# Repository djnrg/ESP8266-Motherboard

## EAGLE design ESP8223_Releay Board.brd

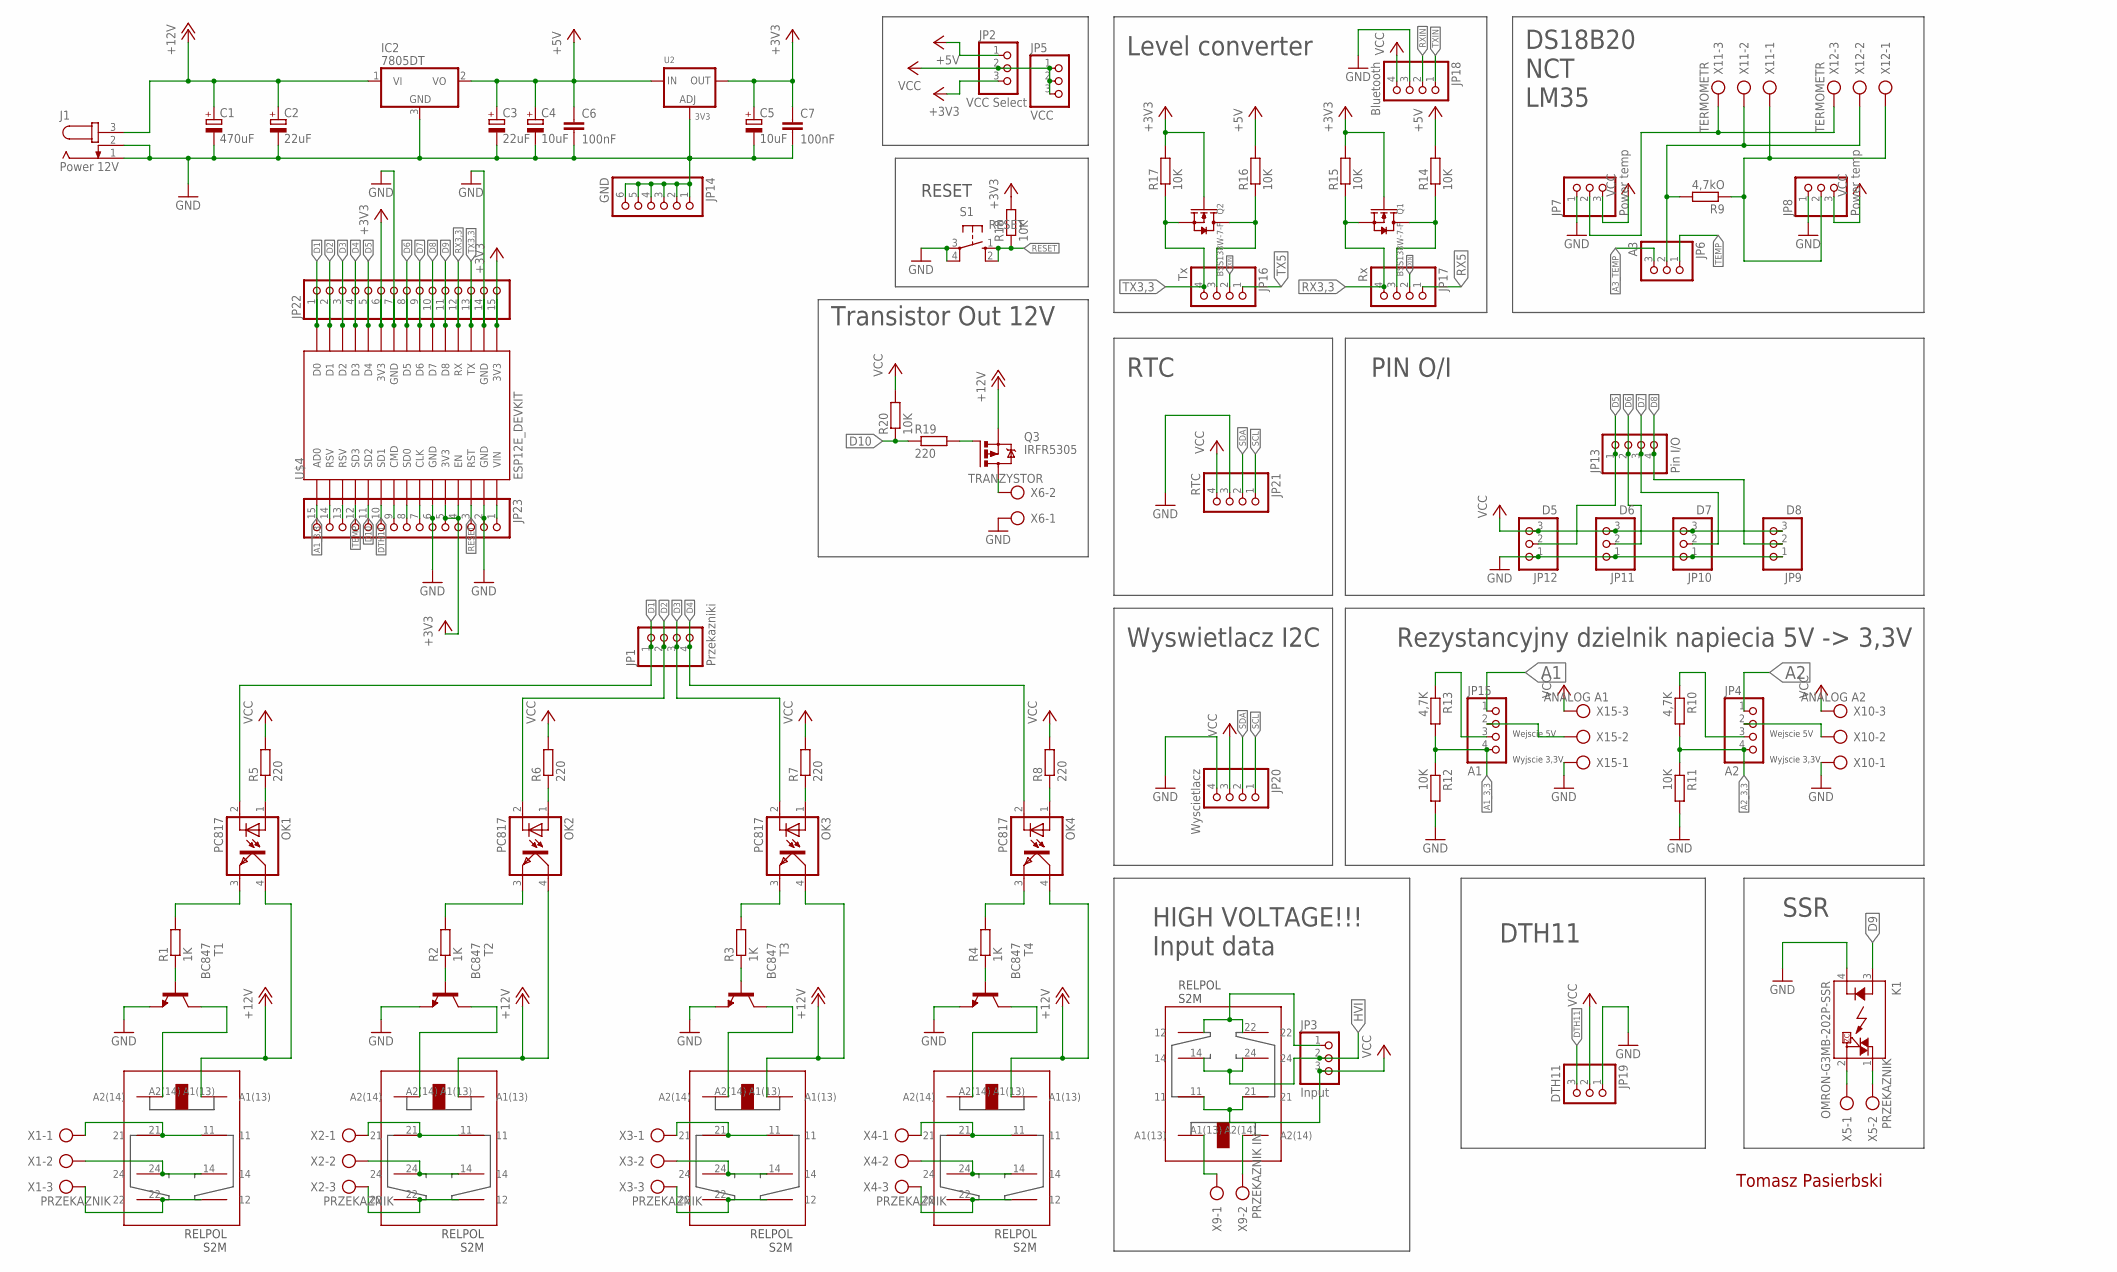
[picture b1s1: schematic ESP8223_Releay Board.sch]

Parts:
C1: 470uF; E5-8,5
C2, C3: 22uF; E2,5-6
C4, C5: 10uF; 153CLV-0810
C6, C7: 100nF; C1206K
IC2: 7805DT; TO252
J1: Power 12V; SPC4077
JP1: Przekazniki; 1X04
JP2: VCC Select; 1X03
JP3: Input; 1X03
JP4: A2; 1X04
JP5: VCC; 1X03
JP6: A3; 1X03
JP7, JP8: Power temp; 1X03
JP9: D8; 1X03
JP10: D7; 1X03
JP11: D6; 1X03
JP12: D5; 1X03
JP13: Pin I/O; 1X04
JP14: GND; 1X06
JP15: A1; 1X04
JP16: Tx; 1X04
JP17: Rx; 1X04
JP18: Bluetooth; 1X04
JP19: DTH11; 1X03
JP20: Wyscietlacz; 1X04
JP21: RTC; 1X04
JP22, JP23: PINHD-1X15; 1X15
K1: OMRON-G3MB-202P-SSR
OK1, OK2, OK3, OK4: PC817; DIL04
Q1, Q2: BSS138W-7-F; SOT-23
Q3: IRFR5305; D-PAK_TO252AA
R1, R2, R3, R4: 1K; R1206W
R5, R6, R7, R8, R19: 220; R1206W
R9: 4,7kO; R1206W
R10, R13: 4,7K; R1206W
R11, R12, R14, R15, R16, R17, R18, R20: 10K; R1206W
S1: RESET; B3F-40XX
T1, T2, T3, T4: BC847; SOT23
U2: 3V3; SOT223-W
U4: RELPOL_S2M; S2M
U$1, U$2, U$3, U$5: RELPOL_S2M; S2M
U$4: ESP12E_DEVKIT
X1, X2, X3, X4: PRZEKAZNIK; AK300/3
X5: PRZEKAZNIK; AK300/2
X6: TRANZYSTOR; AK300/2
X9: PRZEKAZNIK IN; AK300/2
X10: ANALOG A2; AK300/3
X11, X12: TERMOMETR; AK300/3
X15: ANALOG A1; AK300/3

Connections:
+3V3: C5.+, C7.1, JP2.3, JP22.6, JP22.15, JP23.4, JP23.5, Q1.1 (G), Q2.1 (G), R15.2, R17.2, R18.2, U2.2 (OUT), U$4.3V3@0 (3V3), U$4.3V3@1 (3V3), U$4.3V3@2 (3V3), U$4.EN
+5V: C3.+, C4.+, C6.1, IC2.2 (VO), JP2.1, R14.2, R16.2, U2.3 (IN)
+12V: C1.+, C2.+, IC2.1 (VI), J1.3, OK1.4 (COL), OK2.4 (COL), OK3.4 (COL), OK4.4 (COL), Q3.3 (S), U4.A1(13), U$1.A1(13), U$2.A1(13), U$3.A1(13)
A1: JP15.1
A1_3,3: JP15.4, JP23.15, R12.1, R13.2, U$4.AD0
A2: JP4.1
A2_3,3: JP4.4, R10.2, R11.1
A3_TEMP: JP6.3
D1: JP1.1, JP22.1, OK1.2 (C), U$4.D0
D2: JP1.2, JP22.2, OK2.2 (C), U$4.D1
D3: JP1.3, JP22.3, OK3.2 (C), U$4.D2
D4: JP1.4, JP22.4, OK4.2 (C), U$4.D3
D5: JP12.2, JP13.1, JP22.5, U$4.D4
D6: JP11.2, JP13.2, JP22.8, U$4.D5
D7: JP10.2, JP13.3, JP22.9, U$4.D6
D8: JP9.2, JP13.4, JP22.10, U$4.D7
D9: JP22.11, K1.3 (A), U$4.D8
D10: JP23.11, R19.1, R20.1, U$4.SD2
DTH11: JP19.3, JP23.10, U$4.SD1
GND: C1.-, C2.-, C3.-, C4.-, C5.-, C6.2, C7.2, IC2.3 (GND), J1.1, J1.2, JP7.1, JP8.1, JP9.1, JP10.1, JP11.1, JP12.1, JP14.1, JP14.2, JP14.3, JP14.4, JP14.5, JP14.6, JP18.3, JP19.1, JP20.4, JP21.3, JP22.7, JP22.14, JP23.2, JP23.6, K1.4 (K), R11.2, R12.2, S1.3, S1.4 (P1), T1.2 (E), T2.2 (E), T3.2 (E), T4.2 (E), U2.1 (ADJ), U$4.GND@0 (GND), U$4.GND@1 (GND), U$4.GND@2 (GND), U$4.GND@3 (GND), X6.1, X10.1, X15.1
HVI: JP3.2, U$5.14, U$5.24
unnamed: JP23.1, U$4.VIN
unnamed: Q3.1 (G), R19.2
unnamed: JP23.7, U$4.CLK
unnamed: JP23.8, U$4.SD0
unnamed: OK1.1 (A), R5.1
unnamed: OK2.1 (A), R6.1
unnamed: OK3.1 (A), R7.1
unnamed: OK4.1 (A), R8.1
unnamed: JP3.1, U$5.12, U$5.22
unnamed: T2.3 (C), U$1.A2(14)
unnamed: T3.3 (C), U$2.A2(14)
unnamed: T4.3 (C), U$3.A2(14)
unnamed: JP23.9, U$4.CMD
unnamed: T1.3 (C), U4.A2(14)
unnamed: JP4.2, X10.2
unnamed: JP23.13, U$4.RSV@1 (RSV)
unnamed: U$5.A1(13), X9.1
unnamed: R1.1, T1.1 (B)
unnamed: R2.1, T2.1 (B)
unnamed: R3.1, T3.1 (B)
unnamed: R4.1, T4.1 (B)
unnamed: OK1.3 (EMIT), R1.2
unnamed: OK2.3 (EMIT), R2.2
unnamed: OK3.3 (EMIT), R3.2
unnamed: OK4.3 (EMIT), R4.2
unnamed: U$5.A2(14), X9.2
unnamed: JP15.2, X15.2
unnamed: JP23.14, U$4.RSV@0 (RSV)
unnamed: U$3.11, U$3.21, X4.1
unnamed: JP17.3, Q1.3 (D), R14.1
unnamed: U$3.14, U$3.24, X4.2
unnamed: U$3.12, U$3.22, X4.3
unnamed: Q3.4 (D), X6.2
unnamed: JP16.3, Q2.3 (D), R16.1
unnamed: JP7.2, X11.3, X12.3
unnamed: U4.11, U4.21, X1.1
unnamed: U4.14, U4.24, X1.2
unnamed: U4.12, U4.22, X1.3
unnamed: K1.2 (DS2), X5.1
unnamed: K1.1 (DS1), X5.2
unnamed: U$1.11, U$1.21, X2.1
unnamed: U$1.14, U$1.24, X2.2
unnamed: U$1.12, U$1.22, X2.3
unnamed: U$2.11, U$2.21, X3.1
unnamed: U$2.14, U$2.24, X3.2
unnamed: U$2.12, U$2.22, X3.3
unnamed: JP6.2, R9.2, X11.2, X12.2
unnamed: JP8.2, R9.1, X11.1, X12.1
unnamed: JP4.3, R10.1
unnamed: JP15.3, R13.1
RESET: JP23.3, R18.1, S1.1 (S), S1.2 (S1), U$4.RST
RX3,3: JP17.4, JP22.12, Q1.2 (S), R15.1, U$4.RX
RX5: JP17.1
RXIN: JP17.2, JP18.2
SCL: JP20.1, JP21.1
SDA: JP20.2, JP21.2
TEMP: JP6.1, JP23.12, U$4.SD3
TX3,3: JP16.4, JP22.13, Q2.2 (S), R17.1, U$4.TX
TX5: JP16.1
TXIN: JP16.2, JP18.1
VCC: JP2.2, JP3.3, JP5.1, JP5.2, JP5.3, JP7.3, JP8.3, JP9.3, JP10.3, JP11.3, JP12.3, JP18.4, JP19.2, JP20.3, JP21.4, R5.2, R6.2, R7.2, R8.2, R20.2, U$5.11, U$5.21, X10.3, X15.3

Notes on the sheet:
HIGH VOLTAGE!!! Input data
DS18B20 NCT LM35
PIN O/I
Rezystancyjny dzielnik napiecia 5V -> 3,3V
Wejscie 5V
Wyjscie 3,3V
Level converter
SSR
DTH11
RTC
Wyswietlacz I2C
RESET
Transistor Out 12V
Tomasz Pasierbski

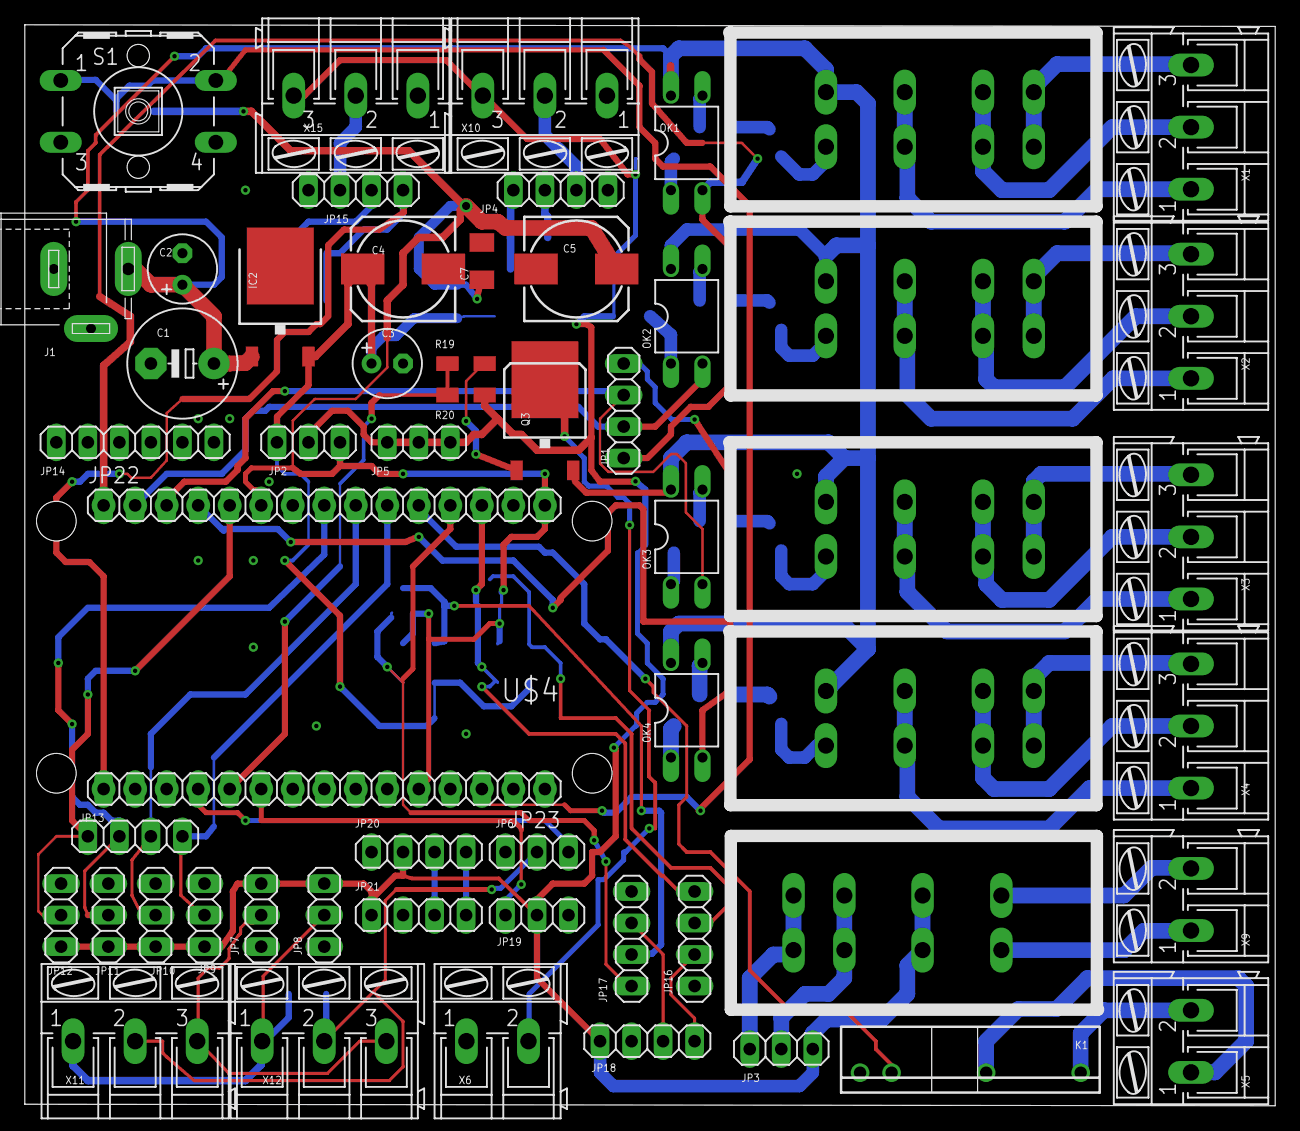
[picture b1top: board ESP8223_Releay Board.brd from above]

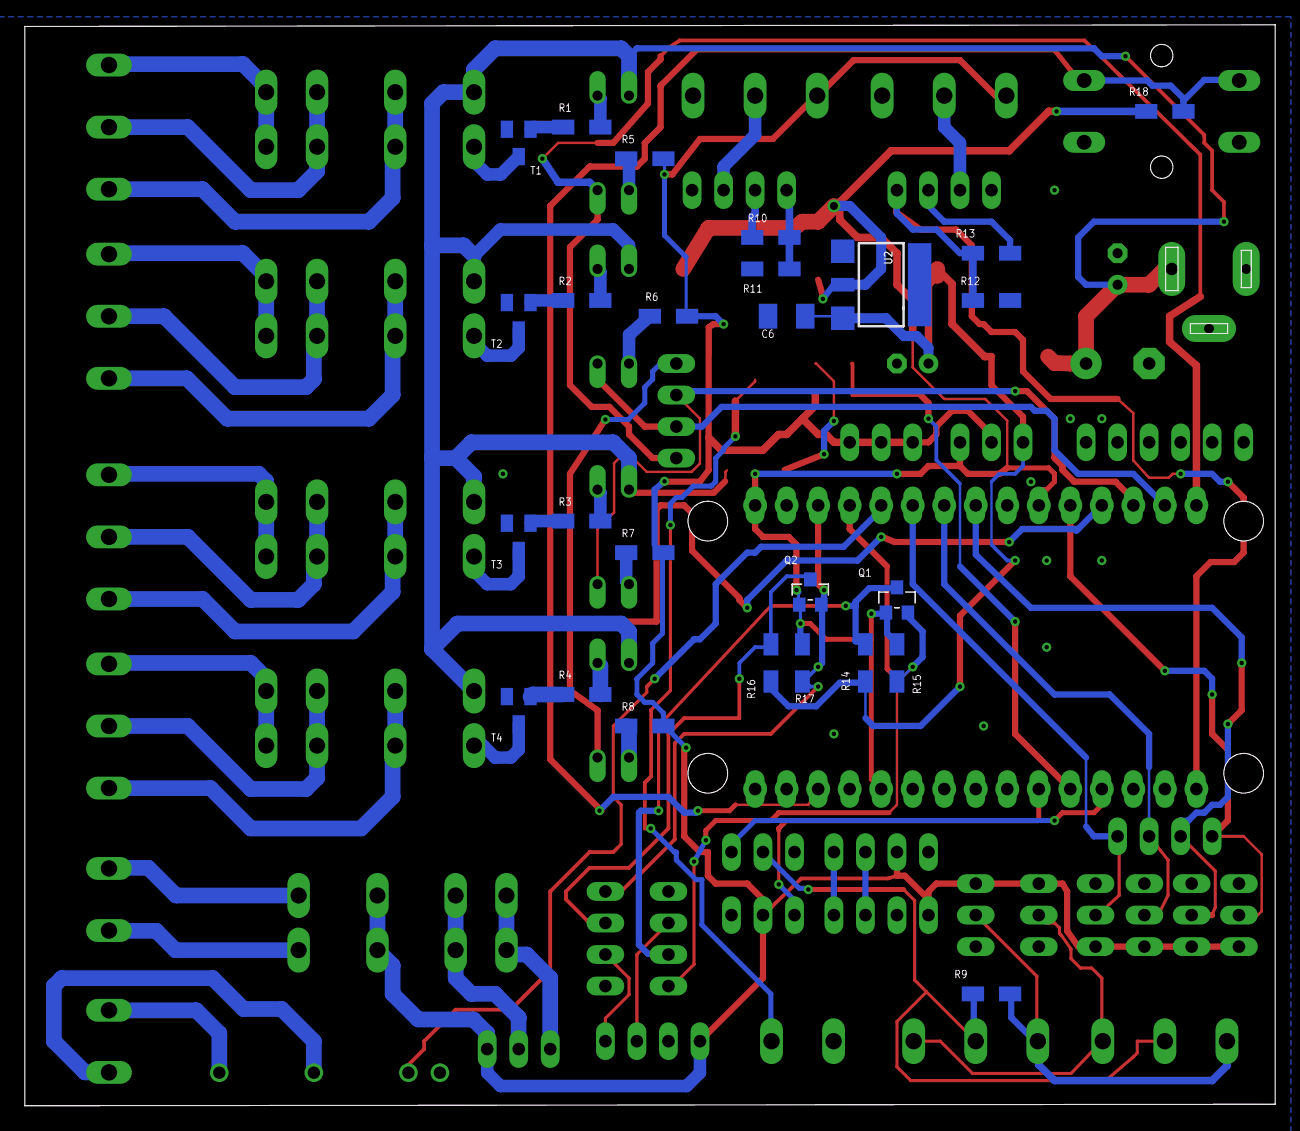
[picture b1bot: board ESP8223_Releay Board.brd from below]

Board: 2 copper layers, 100.8 x 87.1 mm, 83 parts (26 on the bottom side), 77 nets.

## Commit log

2018-12-01 Initial uploads
    Last version

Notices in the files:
parts and their libraries:
microbuilder: This work is placed in the public domain, and may be freely used for commercial and non-commercial work with the following conditions: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
